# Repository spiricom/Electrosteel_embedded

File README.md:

# Electrosteel_embedded
repository for embedded firmware and EAGLE design files for the Electrosteel

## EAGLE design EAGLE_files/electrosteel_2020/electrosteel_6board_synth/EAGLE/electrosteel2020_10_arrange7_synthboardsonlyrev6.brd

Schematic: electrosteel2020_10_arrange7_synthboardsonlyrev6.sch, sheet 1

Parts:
C15, C30: .1uf; C0603K; PARTNO CC0603KRX7R8BB104
C16: 22uf; PANASONIC_D; PARTNO EEE-1CA220NP
C20: 22pf; C0603; PARTNO CC0603JRNPO9BN220
C21, C22, C23, C24, C25, C26, C27, C29, C31, C32: 10uf; C1206K; PARTNO TMK316F106ZL-T
J1: 4P-2.0; HW4-2.0; PARTNO 110990030
J2: 105162-0001; PARTNO 105162-0001
JP12: PINHD-1X2; 1X02; PARTNO *DNP
L1: 2.2uH; BOURNS_SRP2010; PARTNO SRP2010-2R2M
PS1: UWE1215S-3WR3; CONV_UWE1215S-3WR3; PARTNO UWE1215S-3WR3
R1, R2, R8, R13, R16, R19, R22: 10k; R0603; PARTNO ESR03EZPF1002
R3: 560R; R0603; PARTNO ESR03EZPF5600
R5, R93, R94, R95, R96, R97: 47k; R0603; PARTNO ESR03EZPJ473
R6, R7, R9, R12, R14, R15, R17, R18, R20, R21, R23, R56: 2M; R0603; PARTNO RMCF0603FT2M00
R24, R25: 2k; R0603; PARTNO ERJ-PA3F2001V
R27, R29, R30, R31, R32, R33, R34: 47R; R0603; PARTNO RC0603JR-0747RL
S1: 10-XX; B3F-10XX
U1: OPA1611AID; SOIC127P599X175-8N; PARTNO OPA1611AID
U2, U3, U4, U5, U6, U7, U8, U9, U10, U11: ES_DAISY_SEED_DOUBLE; PARTNO 4840-6004-CP
X1: 2516-; PAK100/2500-16; PARTNO SBH11-PBPC-D08-ST-BK

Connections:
+3V3: J2.4 (VDD), R24.1, R25.1, R93.2, R94.2, R95.2, R96.2, R97.2, U7.38 (+3V3_D), U7.B38 (+3V3_D)
+12V: C24.1, L1.P$1, U2.39 (V_IN), U2.B39 (V_IN), U3.39 (V_IN), U3.B39 (V_IN), U4.39 (V_IN), U4.B39 (V_IN), U5.39 (V_IN), U5.B39 (V_IN), U6.39 (V_IN), U6.B39 (V_IN), U7.39 (V_IN), U7.B39 (V_IN), U8.39 (V_IN), U8.B39 (V_IN), U9.39 (V_IN), U9.B39 (V_IN), U10.39 (V_IN), U10.B39 (V_IN), U11.39 (V_IN), U11.B39 (V_IN), X1.1, X1.3
+15V: C30.1, C32.1, PS1.6 (+VO), R6.2, R9.2, R14.2, R17.2, R20.2, R23.2, U1.7 (V+)
-15V: C15.2, C23.2, PS1.8 (-VO), R7.1, R12.1, R15.1, R18.1, R21.1, R56.1, U1.4 (V-)
CLK: J2.5 (CLK), R32.2
CMD: J2.3 (CMD), R31.2
DAT0: J2.7 (DAT0), R33.2
DAT1: J2.8 (DAT1), R34.2
DAT2: J2.1 (DAT2), R29.2
DAT3: J2.2 (CD/DAT3), R30.2
DGND4: C22.2, C24.2, J2.6 (VSS), J2.10 (GND_1), J2.11 (GND_2), J2.12 (GND_3), J2.13 (GND_4), PS1.1 (GND), S1.3, S1.4 (P1), U2.20 (AGND), U2.35 (GPIO28(ADC11)), U2.37 (GPIO30(USB_HS_D+)), U2.40 (GND), U2.B20 (AGND), U2.B35 (GPIO28(ADC11)), U2.B37 (GPIO30(USB_HS_D+)), U2.B40 (GND), U3.20 (AGND), U3.36 (GPIO29(USB_HS_D_-)), U3.37 (GPIO30(USB_HS_D+)), U3.40 (GND), U3.B20 (AGND), U3.B36 (GPIO29(USB_HS_D_-)), U3.B37 (GPIO30(USB_HS_D+)), U3.B40 (GND), U4.20 (AGND), U4.35 (GPIO28(ADC11)), U4.37 (GPIO30(USB_HS_D+)), U4.40 (GND), U4.B20 (AGND), U4.B35 (GPIO28(ADC11)), U4.B37 (GPIO30(USB_HS_D+)), U4.B40 (GND), U5.20 (AGND), U5.37 (GPIO30(USB_HS_D+)), U5.40 (GND), U5.B20 (AGND), U5.B37 (GPIO30(USB_HS_D+)), U5.B40 (GND), U6.20 (AGND), U6.35 (GPIO28(ADC11)), U6.36 (GPIO29(USB_HS_D_-)), U6.40 (GND), U6.B20 (AGND), U6.B35 (GPIO28(ADC11)), U6.B36 (GPIO29(USB_HS_D_-)), U6.B40 (GND), U7.20 (AGND), U7.35 (GPIO28(ADC11)), U7.36 (GPIO29(USB_HS_D_-)), U7.37 (GPIO30(USB_HS_D+)), U7.40 (GND), U7.B20 (AGND), U7.B35 (GPIO28(ADC11)), U7.B36 (GPIO29(USB_HS_D_-)), U7.B37 (GPIO30(USB_HS_D+)), U7.B40 (GND), U8.20 (AGND), U8.36 (GPIO29(USB_HS_D_-)), U8.40 (GND), U8.B20 (AGND), U8.B36 (GPIO29(USB_HS_D_-)), U8.B40 (GND), U9.20 (AGND), U9.37 (GPIO30(USB_HS_D+)), U9.40 (GND), U9.B20 (AGND), U9.B37 (GPIO30(USB_HS_D+)), U9.B40 (GND), U10.20 (AGND), U10.35 (GPIO28(ADC11)), U10.36 (GPIO29(USB_HS_D_-)), U10.40 (GND), U10.B20 (AGND), U10.B35 (GPIO28(ADC11)), U10.B36 (GPIO29(USB_HS_D_-)), U10.B40 (GND), U11.20 (AGND), U11.36 (GPIO29(USB_HS_D_-)), U11.40 (GND), U11.B20 (AGND), U11.B36 (GPIO29(USB_HS_D_-)), U11.B40 (GND), X1.2, X1.4
GNDINT: C15.1, C23.1, C30.2, C32.2, J1.3, J1.4, JP12.2, PS1.7 (0V), R5.1, U1.3 (+IN)
I2C_SCL: R24.2, U2.12 (GPIO11(I2C1_SCL)), U2.B12 (GPIO11(I2C1_SCL)), U3.12 (GPIO11(I2C1_SCL)), U3.B12 (GPIO11(I2C1_SCL)), U4.12 (GPIO11(I2C1_SCL)), U4.B12 (GPIO11(I2C1_SCL)), U5.12 (GPIO11(I2C1_SCL)), U5.B12 (GPIO11(I2C1_SCL)), U6.12 (GPIO11(I2C1_SCL)), U6.B12 (GPIO11(I2C1_SCL)), U7.12 (GPIO11(I2C1_SCL)), U7.B12 (GPIO11(I2C1_SCL)), U8.12 (GPIO11(I2C1_SCL)), U8.B12 (GPIO11(I2C1_SCL)), U9.12 (GPIO11(I2C1_SCL)), U9.B12 (GPIO11(I2C1_SCL)), U10.12 (GPIO11(I2C1_SCL)), U10.B12 (GPIO11(I2C1_SCL)), U11.12 (GPIO11(I2C1_SCL)), U11.B12 (GPIO11(I2C1_SCL))
I2C_SDA: R25.2, U2.13 (GPIO12(I2C1_SDA)), U2.B13 (GPIO12(I2C1_SDA)), U3.13 (GPIO12(I2C1_SDA)), U3.B13 (GPIO12(I2C1_SDA)), U4.13 (GPIO12(I2C1_SDA)), U4.B13 (GPIO12(I2C1_SDA)), U5.13 (GPIO12(I2C1_SDA)), U5.B13 (GPIO12(I2C1_SDA)), U6.13 (GPIO12(I2C1_SDA)), U6.B13 (GPIO12(I2C1_SDA)), U7.13 (GPIO12(I2C1_SDA)), U7.B13 (GPIO12(I2C1_SDA)), U8.13 (GPIO12(I2C1_SDA)), U8.B13 (GPIO12(I2C1_SDA)), U9.13 (GPIO12(I2C1_SDA)), U9.B13 (GPIO12(I2C1_SDA)), U10.13 (GPIO12(I2C1_SDA)), U10.B13 (GPIO12(I2C1_SDA)), U11.13 (GPIO12(I2C1_SDA)), U11.B13 (GPIO12(I2C1_SDA))
MASTER_SIGNAL: U2.1 (GPIO0(USB_HS_ID)), U2.B1 (GPIO0(USB_HS_ID)), U3.1 (GPIO0(USB_HS_ID)), U3.B1 (GPIO0(USB_HS_ID)), U4.1 (GPIO0(USB_HS_ID)), U4.B1 (GPIO0(USB_HS_ID)), U5.1 (GPIO0(USB_HS_ID)), U5.B1 (GPIO0(USB_HS_ID)), U6.1 (GPIO0(USB_HS_ID)), U6.B1 (GPIO0(USB_HS_ID)), U7.1 (GPIO0(USB_HS_ID)), U7.B1 (GPIO0(USB_HS_ID)), U8.1 (GPIO0(USB_HS_ID)), U8.B1 (GPIO0(USB_HS_ID)), U9.1 (GPIO0(USB_HS_ID)), U9.B1 (GPIO0(USB_HS_ID)), U10.1 (GPIO0(USB_HS_ID)), U10.B1 (GPIO0(USB_HS_ID)), U11.1 (GPIO0(USB_HS_ID)), U11.B1 (GPIO0(USB_HS_ID))
MISO_2: R27.1, U7.10 (GPIO9(SPI1_MISO)), U7.B10 (GPIO9(SPI1_MISO))
MISO_2_P1: U3.10 (GPIO9(SPI1_MISO)), U3.B10 (GPIO9(SPI1_MISO))
MISO_2_P2: U4.10 (GPIO9(SPI1_MISO)), U4.B10 (GPIO9(SPI1_MISO))
MISO_2_P3: U5.10 (GPIO9(SPI1_MISO)), U5.B10 (GPIO9(SPI1_MISO))
MISO_2_P4: U6.10 (GPIO9(SPI1_MISO)), U6.B10 (GPIO9(SPI1_MISO))
MISO_2_P5: U8.10 (GPIO9(SPI1_MISO)), U8.B10 (GPIO9(SPI1_MISO))
MISO_2_P6: U2.10 (GPIO9(SPI1_MISO)), U2.B10 (GPIO9(SPI1_MISO))
MISO_2_P7: U9.10 (GPIO9(SPI1_MISO)), U9.B10 (GPIO9(SPI1_MISO))
MISO_2_P8: U10.10 (GPIO9(SPI1_MISO)), U10.B10 (GPIO9(SPI1_MISO))
MISO_2_P9: U11.10 (GPIO9(SPI1_MISO)), U11.B10 (GPIO9(SPI1_MISO))
MONO_OUTPUT: C16.+, C20.2, R2.2, U1.6 (OUT)
MOSI_2: U2.11 (GPIO10(SPI1_MOSI)), U2.B11 (GPIO10(SPI1_MOSI)), U3.11 (GPIO10(SPI1_MOSI)), U3.B11 (GPIO10(SPI1_MOSI)), U4.11 (GPIO10(SPI1_MOSI)), U4.B11 (GPIO10(SPI1_MOSI)), U5.11 (GPIO10(SPI1_MOSI)), U5.B11 (GPIO10(SPI1_MOSI)), U6.11 (GPIO10(SPI1_MOSI)), U6.B11 (GPIO10(SPI1_MOSI)), U7.11 (GPIO10(SPI1_MOSI)), U7.B11 (GPIO10(SPI1_MOSI)), U8.11 (GPIO10(SPI1_MOSI)), U8.B11 (GPIO10(SPI1_MOSI)), U9.11 (GPIO10(SPI1_MOSI)), U9.B11 (GPIO10(SPI1_MOSI)), U10.11 (GPIO10(SPI1_MOSI)), U10.B11 (GPIO10(SPI1_MOSI)), U11.11 (GPIO10(SPI1_MOSI)), U11.B11 (GPIO10(SPI1_MOSI)), X1.12
unnamed: U5.31 (GPIO24(ADC9)), U5.B31 (GPIO24(ADC9))
unnamed: C21.2, R6.1, R7.2, R8.1
unnamed: U6.31 (GPIO24(ADC9)), U6.B31 (GPIO24(ADC9))
unnamed: C20.1, R1.2, R2.1, R8.2, R13.2, R16.2, R19.2, R22.2, U1.2 (-IN)
unnamed: C16.-, R3.1
unnamed: J1.1, J1.2, JP12.1, R3.2, R5.2
unnamed: C25.2, R1.1, R23.1, R56.2
unnamed: C26.2, R9.1, R12.2, R13.1
unnamed: C27.2, R14.1, R15.2, R16.1
unnamed: C29.2, R17.1, R18.2, R19.1
unnamed: C31.2, R20.1, R21.2, R22.1
unnamed: U7.19 (AUDIO_OUT_R), U7.B19 (AUDIO_OUT_R)
unnamed: U7.17 (AUDIO_IN_R), U7.B17 (AUDIO_IN_R)
unnamed: U7.16 (AUDIO_IN_L), U7.B16 (AUDIO_IN_L)
unnamed: U7.15 (GPIO14(USART1_RX)), U7.B15 (GPIO14(USART1_RX))
unnamed: U2.21 (+3V3_A), U2.B21 (+3V3_A)
unnamed: U8.31 (GPIO24(ADC9)), U8.B31 (GPIO24(ADC9))
unnamed: U8.26 (GPIO19(ADC4)), U8.B26 (GPIO19(ADC4))
unnamed: U6.26 (GPIO19(ADC4)), U6.B26 (GPIO19(ADC4))
unnamed: U7.34 (GPIO27(SAI2_FS_B)), U7.B34 (GPIO27(SAI2_FS_B))
unnamed: U7.33 (GPIO26(SAI2_SD_A)), U7.B33 (GPIO26(SAI2_SD_A))
unnamed: U7.32 (GPIO25(ADC10)), U7.B32 (GPIO25(ADC10))
unnamed: U5.26 (GPIO19(ADC4)), U5.B26 (GPIO19(ADC4))
unnamed: R27.2, X1.11
unnamed: U7.28 (GPIO21(ADC6)), U7.B28 (GPIO21(ADC6))
unnamed: U7.27 (GPIO20(ADC5)), U7.B27 (GPIO20(ADC5))
unnamed: U4.26 (GPIO19(ADC4)), U4.B26 (GPIO19(ADC4))
unnamed: U3.26 (GPIO19(ADC4)), U3.B26 (GPIO19(ADC4))
unnamed: U3.21 (+3V3_A), U3.B21 (+3V3_A)
unnamed: U7.24 (GPIO17(ADC2)), U7.B24 (GPIO17(ADC2))
unnamed: U7.23 (GPIO16(ADC1)), U7.B23 (GPIO16(ADC1))
unnamed: U7.22 (GPIO15(ADC0)), U7.B22 (GPIO15(ADC0))
unnamed: U3.19 (AUDIO_OUT_R), U3.B19 (AUDIO_OUT_R)
unnamed: U3.17 (AUDIO_IN_R), U3.B17 (AUDIO_IN_R)
unnamed: U3.16 (AUDIO_IN_L), U3.B16 (AUDIO_IN_L)
unnamed: U3.15 (GPIO14(USART1_RX)), U3.B15 (GPIO14(USART1_RX))
unnamed: U3.14 (GPIO13(USART1_TX)), U3.B14 (GPIO13(USART1_TX))
unnamed: U7.26 (GPIO19(ADC4)), U7.B26 (GPIO19(ADC4))
unnamed: U3.35 (GPIO28(ADC11)), U3.38 (+3V3_D), U3.B35 (GPIO28(ADC11)), U3.B38 (+3V3_D)
unnamed: U3.34 (GPIO27(SAI2_FS_B)), U3.B34 (GPIO27(SAI2_FS_B))
unnamed: U3.33 (GPIO26(SAI2_SD_A)), U3.B33 (GPIO26(SAI2_SD_A))
unnamed: U3.32 (GPIO25(ADC10)), U3.B32 (GPIO25(ADC10))
unnamed: U3.28 (GPIO21(ADC6)), U3.B28 (GPIO21(ADC6))
unnamed: U3.27 (GPIO20(ADC5)), U3.B27 (GPIO20(ADC5))
unnamed: U7.21 (+3V3_A), U7.B21 (+3V3_A)
unnamed: U3.24 (GPIO17(ADC2)), U3.B24 (GPIO17(ADC2))
unnamed: U3.23 (GPIO16(ADC1)), U3.B23 (GPIO16(ADC1))
unnamed: U3.22 (GPIO15(ADC0)), U3.B22 (GPIO15(ADC0))
unnamed: U4.21 (+3V3_A), U4.B21 (+3V3_A)
unnamed: U4.19 (AUDIO_OUT_R), U4.B19 (AUDIO_OUT_R)
unnamed: U4.17 (AUDIO_IN_R), U4.B17 (AUDIO_IN_R)
unnamed: U4.16 (AUDIO_IN_L), U4.B16 (AUDIO_IN_L)
unnamed: U4.15 (GPIO14(USART1_RX)), U4.B15 (GPIO14(USART1_RX))
unnamed: U4.14 (GPIO13(USART1_TX)), U4.B14 (GPIO13(USART1_TX))
unnamed: S1.1 (S), S1.2 (S1), U7.14 (GPIO13(USART1_TX)), U7.B14 (GPIO13(USART1_TX))
unnamed: U3.2 (GPIO1(SDMMC1_D3)), U3.B2 (GPIO1(SDMMC1_D3))
unnamed: U4.34 (GPIO27(SAI2_FS_B)), U4.B34 (GPIO27(SAI2_FS_B))
unnamed: U4.33 (GPIO26(SAI2_SD_A)), U4.B33 (GPIO26(SAI2_SD_A))
unnamed: U4.32 (GPIO25(ADC10)), U4.B32 (GPIO25(ADC10))
unnamed: U4.28 (GPIO21(ADC6)), U4.B28 (GPIO21(ADC6))
unnamed: U4.27 (GPIO20(ADC5)), U4.B27 (GPIO20(ADC5))
unnamed: U4.24 (GPIO17(ADC2)), U4.B24 (GPIO17(ADC2))
unnamed: U4.23 (GPIO16(ADC1)), U4.B23 (GPIO16(ADC1))
unnamed: U4.22 (GPIO15(ADC0)), U4.B22 (GPIO15(ADC0))
unnamed: U5.21 (+3V3_A), U5.B21 (+3V3_A)
unnamed: U5.19 (AUDIO_OUT_R), U5.B19 (AUDIO_OUT_R)
unnamed: U5.17 (AUDIO_IN_R), U5.B17 (AUDIO_IN_R)
unnamed: U5.16 (AUDIO_IN_L), U5.B16 (AUDIO_IN_L)
unnamed: U5.15 (GPIO14(USART1_RX)), U5.B15 (GPIO14(USART1_RX))
unnamed: U5.14 (GPIO13(USART1_TX)), U5.B14 (GPIO13(USART1_TX))
unnamed: U3.3 (GPIO2(SDMMC1_D2)), U3.B3 (GPIO2(SDMMC1_D2))
unnamed: U3.4 (GPIO3(SDMMC1_D1)), U3.B4 (GPIO3(SDMMC1_D1))
unnamed: U5.34 (GPIO27(SAI2_FS_B)), U5.B34 (GPIO27(SAI2_FS_B))
unnamed: U5.33 (GPIO26(SAI2_SD_A)), U5.B33 (GPIO26(SAI2_SD_A))
unnamed: U5.32 (GPIO25(ADC10)), U5.B32 (GPIO25(ADC10))
unnamed: U5.28 (GPIO21(ADC6)), U5.B28 (GPIO21(ADC6))
unnamed: U5.27 (GPIO20(ADC5)), U5.B27 (GPIO20(ADC5))
unnamed: U5.24 (GPIO17(ADC2)), U5.B24 (GPIO17(ADC2))
unnamed: U5.23 (GPIO16(ADC1)), U5.B23 (GPIO16(ADC1))
unnamed: U5.22 (GPIO15(ADC0)), U5.B22 (GPIO15(ADC0))
unnamed: C22.1, L1.P$2, PS1.2 (VIN)
unnamed: U6.21 (+3V3_A), U6.B21 (+3V3_A)
unnamed: U6.19 (AUDIO_OUT_R), U6.B19 (AUDIO_OUT_R)
unnamed: U6.17 (AUDIO_IN_R), U6.B17 (AUDIO_IN_R)
unnamed: U6.16 (AUDIO_IN_L), U6.B16 (AUDIO_IN_L)
unnamed: U6.15 (GPIO14(USART1_RX)), U6.B15 (GPIO14(USART1_RX))
unnamed: U6.14 (GPIO13(USART1_TX)), U6.B14 (GPIO13(USART1_TX))
unnamed: U6.37 (GPIO30(USB_HS_D+)), U6.38 (+3V3_D), U6.B37 (GPIO30(USB_HS_D+)), U6.B38 (+3V3_D)
unnamed: U3.5 (GPIO4(SDMMC1_D0)), U3.B5 (GPIO4(SDMMC1_D0))
unnamed: U6.34 (GPIO27(SAI2_FS_B)), U6.B34 (GPIO27(SAI2_FS_B))
unnamed: U6.33 (GPIO26(SAI2_SD_A)), U6.B33 (GPIO26(SAI2_SD_A))
unnamed: U6.32 (GPIO25(ADC10)), U6.B32 (GPIO25(ADC10))
unnamed: U6.28 (GPIO21(ADC6)), U6.B28 (GPIO21(ADC6))
unnamed: U6.27 (GPIO20(ADC5)), U6.B27 (GPIO20(ADC5))
unnamed: U6.24 (GPIO17(ADC2)), U6.B24 (GPIO17(ADC2))
unnamed: U6.23 (GPIO16(ADC1)), U6.B23 (GPIO16(ADC1))
unnamed: U6.22 (GPIO15(ADC0)), U6.B22 (GPIO15(ADC0))
unnamed: U8.21 (+3V3_A), U8.B21 (+3V3_A)
unnamed: U8.19 (AUDIO_OUT_R), U8.B19 (AUDIO_OUT_R)
unnamed: U8.17 (AUDIO_IN_R), U8.B17 (AUDIO_IN_R)
unnamed: U8.16 (AUDIO_IN_L), U8.B16 (AUDIO_IN_L)
unnamed: U8.15 (GPIO14(USART1_RX)), U8.B15 (GPIO14(USART1_RX))
unnamed: U8.14 (GPIO13(USART1_TX)), U8.B14 (GPIO13(USART1_TX))
unnamed: U8.35 (GPIO28(ADC11)), U8.37 (GPIO30(USB_HS_D+)), U8.38 (+3V3_D), U8.B35 (GPIO28(ADC11)), U8.B37 (GPIO30(USB_HS_D+)), U8.B38 (+3V3_D)
unnamed: U3.6 (GPIO5(SDMMC1_CMD)), U3.B6 (GPIO5(SDMMC1_CMD))
unnamed: U3.7 (GPIO6(SDMMC1_CK)), U3.B7 (GPIO6(SDMMC1_CK))
unnamed: U2.19 (AUDIO_OUT_R), U2.B19 (AUDIO_OUT_R)
unnamed: U8.34 (GPIO27(SAI2_FS_B)), U8.B34 (GPIO27(SAI2_FS_B))
unnamed: U8.33 (GPIO26(SAI2_SD_A)), U8.B33 (GPIO26(SAI2_SD_A))
unnamed: U8.32 (GPIO25(ADC10)), U8.B32 (GPIO25(ADC10))
unnamed: U8.28 (GPIO21(ADC6)), U8.B28 (GPIO21(ADC6))
unnamed: U8.27 (GPIO20(ADC5)), U8.B27 (GPIO20(ADC5))
unnamed: U8.24 (GPIO17(ADC2)), U8.B24 (GPIO17(ADC2))
unnamed: U8.23 (GPIO16(ADC1)), U8.B23 (GPIO16(ADC1))
unnamed: U8.22 (GPIO15(ADC0)), U8.B22 (GPIO15(ADC0))
unnamed: U4.2 (GPIO1(SDMMC1_D3)), U4.B2 (GPIO1(SDMMC1_D3))
unnamed: U4.3 (GPIO2(SDMMC1_D2)), U4.B3 (GPIO2(SDMMC1_D2))
unnamed: U4.4 (GPIO3(SDMMC1_D1)), U4.B4 (GPIO3(SDMMC1_D1))
unnamed: U4.5 (GPIO4(SDMMC1_D0)), U4.B5 (GPIO4(SDMMC1_D0))
unnamed: U4.6 (GPIO5(SDMMC1_CMD)), U4.B6 (GPIO5(SDMMC1_CMD))
unnamed: U4.7 (GPIO6(SDMMC1_CK)), U4.B7 (GPIO6(SDMMC1_CK))
unnamed: U2.17 (AUDIO_IN_R), U2.B17 (AUDIO_IN_R)
unnamed: U5.2 (GPIO1(SDMMC1_D3)), U5.B2 (GPIO1(SDMMC1_D3))
unnamed: U5.3 (GPIO2(SDMMC1_D2)), U5.B3 (GPIO2(SDMMC1_D2))
unnamed: U5.4 (GPIO3(SDMMC1_D1)), U5.B4 (GPIO3(SDMMC1_D1))
unnamed: U5.5 (GPIO4(SDMMC1_D0)), U5.B5 (GPIO4(SDMMC1_D0))
unnamed: U5.6 (GPIO5(SDMMC1_CMD)), U5.B6 (GPIO5(SDMMC1_CMD))
unnamed: U5.7 (GPIO6(SDMMC1_CK)), U5.B7 (GPIO6(SDMMC1_CK))
unnamed: U2.16 (AUDIO_IN_L), U2.B16 (AUDIO_IN_L)
unnamed: U6.2 (GPIO1(SDMMC1_D3)), U6.B2 (GPIO1(SDMMC1_D3))
unnamed: U6.3 (GPIO2(SDMMC1_D2)), U6.B3 (GPIO2(SDMMC1_D2))
unnamed: U6.4 (GPIO3(SDMMC1_D1)), U6.B4 (GPIO3(SDMMC1_D1))
unnamed: U6.5 (GPIO4(SDMMC1_D0)), U6.B5 (GPIO4(SDMMC1_D0))
unnamed: U6.6 (GPIO5(SDMMC1_CMD)), U6.B6 (GPIO5(SDMMC1_CMD))
unnamed: U6.7 (GPIO6(SDMMC1_CK)), U6.B7 (GPIO6(SDMMC1_CK))
unnamed: U8.2 (GPIO1(SDMMC1_D3)), U8.B2 (GPIO1(SDMMC1_D3))
unnamed: U8.3 (GPIO2(SDMMC1_D2)), U8.B3 (GPIO2(SDMMC1_D2))
unnamed: U8.4 (GPIO3(SDMMC1_D1)), U8.B4 (GPIO3(SDMMC1_D1))
unnamed: U8.5 (GPIO4(SDMMC1_D0)), U8.B5 (GPIO4(SDMMC1_D0))
unnamed: U8.6 (GPIO5(SDMMC1_CMD)), U8.B6 (GPIO5(SDMMC1_CMD))
unnamed: U8.7 (GPIO6(SDMMC1_CK)), U8.B7 (GPIO6(SDMMC1_CK))
unnamed: U2.15 (GPIO14(USART1_RX)), U2.B15 (GPIO14(USART1_RX))
unnamed: U2.14 (GPIO13(USART1_TX)), U2.B14 (GPIO13(USART1_TX))
unnamed: U2.34 (GPIO27(SAI2_FS_B)), U2.B34 (GPIO27(SAI2_FS_B))
unnamed: U2.33 (GPIO26(SAI2_SD_A)), U2.B33 (GPIO26(SAI2_SD_A))
unnamed: U2.32 (GPIO25(ADC10)), U2.B32 (GPIO25(ADC10))
unnamed: U2.28 (GPIO21(ADC6)), U2.B28 (GPIO21(ADC6))
unnamed: U2.27 (GPIO20(ADC5)), U2.B27 (GPIO20(ADC5))
unnamed: U2.24 (GPIO17(ADC2)), U2.B24 (GPIO17(ADC2))
unnamed: U2.23 (GPIO16(ADC1)), U2.B23 (GPIO16(ADC1))
unnamed: U2.22 (GPIO15(ADC0)), U2.B22 (GPIO15(ADC0))
unnamed: U9.21 (+3V3_A), U9.B21 (+3V3_A)
unnamed: U9.19 (AUDIO_OUT_R), U9.B19 (AUDIO_OUT_R)
unnamed: U9.17 (AUDIO_IN_R), U9.B17 (AUDIO_IN_R)
unnamed: U9.16 (AUDIO_IN_L), U9.B16 (AUDIO_IN_L)
unnamed: U9.15 (GPIO14(USART1_RX)), U9.B15 (GPIO14(USART1_RX))
unnamed: U9.14 (GPIO13(USART1_TX)), U9.B14 (GPIO13(USART1_TX))
unnamed: U9.34 (GPIO27(SAI2_FS_B)), U9.B34 (GPIO27(SAI2_FS_B))
unnamed: U9.33 (GPIO26(SAI2_SD_A)), U9.B33 (GPIO26(SAI2_SD_A))
unnamed: U9.32 (GPIO25(ADC10)), U9.B32 (GPIO25(ADC10))
unnamed: U9.28 (GPIO21(ADC6)), U9.B28 (GPIO21(ADC6))
unnamed: U9.27 (GPIO20(ADC5)), U9.B27 (GPIO20(ADC5))
unnamed: U9.24 (GPIO17(ADC2)), U9.B24 (GPIO17(ADC2))
unnamed: U9.23 (GPIO16(ADC1)), U9.B23 (GPIO16(ADC1))
unnamed: U9.22 (GPIO15(ADC0)), U9.B22 (GPIO15(ADC0))
unnamed: U10.21 (+3V3_A), U10.B21 (+3V3_A)
unnamed: U10.19 (AUDIO_OUT_R), U10.B19 (AUDIO_OUT_R)
unnamed: U10.17 (AUDIO_IN_R), U10.B17 (AUDIO_IN_R)
unnamed: U10.16 (AUDIO_IN_L), U10.B16 (AUDIO_IN_L)
unnamed: U10.15 (GPIO14(USART1_RX)), U10.B15 (GPIO14(USART1_RX))
unnamed: U10.14 (GPIO13(USART1_TX)), U10.B14 (GPIO13(USART1_TX))
unnamed: U10.37 (GPIO30(USB_HS_D+)), U10.38 (+3V3_D), U10.B37 (GPIO30(USB_HS_D+)), U10.B38 (+3V3_D)
unnamed: U10.34 (GPIO27(SAI2_FS_B)), U10.B34 (GPIO27(SAI2_FS_B))
unnamed: U10.33 (GPIO26(SAI2_SD_A)), U10.B33 (GPIO26(SAI2_SD_A))
unnamed: U10.32 (GPIO25(ADC10)), U10.B32 (GPIO25(ADC10))
unnamed: U10.28 (GPIO21(ADC6)), U10.B28 (GPIO21(ADC6))
unnamed: U10.27 (GPIO20(ADC5)), U10.B27 (GPIO20(ADC5))
unnamed: U10.24 (GPIO17(ADC2)), U10.B24 (GPIO17(ADC2))
unnamed: U10.23 (GPIO16(ADC1)), U10.B23 (GPIO16(ADC1))
unnamed: U10.22 (GPIO15(ADC0)), U10.B22 (GPIO15(ADC0))
unnamed: U11.21 (+3V3_A), U11.B21 (+3V3_A)
unnamed: U11.19 (AUDIO_OUT_R), U11.B19 (AUDIO_OUT_R)
unnamed: U11.17 (AUDIO_IN_R), U11.B17 (AUDIO_IN_R)
unnamed: U11.16 (AUDIO_IN_L), U11.B16 (AUDIO_IN_L)
unnamed: U11.15 (GPIO14(USART1_RX)), U11.B15 (GPIO14(USART1_RX))
unnamed: U11.14 (GPIO13(USART1_TX)), U11.B14 (GPIO13(USART1_TX))
unnamed: U11.35 (GPIO28(ADC11)), U11.37 (GPIO30(USB_HS_D+)), U11.38 (+3V3_D), U11.B35 (GPIO28(ADC11)), U11.B37 (GPIO30(USB_HS_D+)), U11.B38 (+3V3_D)
unnamed: U11.34 (GPIO27(SAI2_FS_B)), U11.B34 (GPIO27(SAI2_FS_B))
unnamed: U11.33 (GPIO26(SAI2_SD_A)), U11.B33 (GPIO26(SAI2_SD_A))
unnamed: U11.32 (GPIO25(ADC10)), U11.B32 (GPIO25(ADC10))
unnamed: U11.28 (GPIO21(ADC6)), U11.B28 (GPIO21(ADC6))
unnamed: U11.27 (GPIO20(ADC5)), U11.B27 (GPIO20(ADC5))
unnamed: U11.24 (GPIO17(ADC2)), U11.B24 (GPIO17(ADC2))
unnamed: U11.23 (GPIO16(ADC1)), U11.B23 (GPIO16(ADC1))
unnamed: U11.22 (GPIO15(ADC0)), U11.B22 (GPIO15(ADC0))
unnamed: U9.31 (GPIO24(ADC9)), U9.B31 (GPIO24(ADC9))
unnamed: U10.31 (GPIO24(ADC9)), U10.B31 (GPIO24(ADC9))
unnamed: U11.31 (GPIO24(ADC9)), U11.B31 (GPIO24(ADC9))
unnamed: U11.26 (GPIO19(ADC4)), U11.B26 (GPIO19(ADC4))
unnamed: U10.26 (GPIO19(ADC4)), U10.B26 (GPIO19(ADC4))
unnamed: U9.26 (GPIO19(ADC4)), U9.B26 (GPIO19(ADC4))
unnamed: U2.26 (GPIO19(ADC4)), U2.B26 (GPIO19(ADC4))
unnamed: U2.2 (GPIO1(SDMMC1_D3)), U2.B2 (GPIO1(SDMMC1_D3))
unnamed: U2.3 (GPIO2(SDMMC1_D2)), U2.B3 (GPIO2(SDMMC1_D2))
unnamed: U2.4 (GPIO3(SDMMC1_D1)), U2.B4 (GPIO3(SDMMC1_D1))
unnamed: U2.5 (GPIO4(SDMMC1_D0)), U2.B5 (GPIO4(SDMMC1_D0))
unnamed: U2.6 (GPIO5(SDMMC1_CMD)), U2.B6 (GPIO5(SDMMC1_CMD))
unnamed: U2.7 (GPIO6(SDMMC1_CK)), U2.B7 (GPIO6(SDMMC1_CK))
unnamed: U9.2 (GPIO1(SDMMC1_D3)), U9.B2 (GPIO1(SDMMC1_D3))
unnamed: U9.3 (GPIO2(SDMMC1_D2)), U9.B3 (GPIO2(SDMMC1_D2))
unnamed: U9.4 (GPIO3(SDMMC1_D1)), U9.B4 (GPIO3(SDMMC1_D1))
unnamed: U9.5 (GPIO4(SDMMC1_D0)), U9.B5 (GPIO4(SDMMC1_D0))
unnamed: U9.6 (GPIO5(SDMMC1_CMD)), U9.B6 (GPIO5(SDMMC1_CMD))
unnamed: U9.7 (GPIO6(SDMMC1_CK)), U9.B7 (GPIO6(SDMMC1_CK))
unnamed: U10.2 (GPIO1(SDMMC1_D3)), U10.B2 (GPIO1(SDMMC1_D3))
unnamed: U10.3 (GPIO2(SDMMC1_D2)), U10.B3 (GPIO2(SDMMC1_D2))
unnamed: U10.4 (GPIO3(SDMMC1_D1)), U10.B4 (GPIO3(SDMMC1_D1))
unnamed: U10.5 (GPIO4(SDMMC1_D0)), U10.B5 (GPIO4(SDMMC1_D0))
unnamed: U10.6 (GPIO5(SDMMC1_CMD)), U10.B6 (GPIO5(SDMMC1_CMD))
unnamed: U10.7 (GPIO6(SDMMC1_CK)), U10.B7 (GPIO6(SDMMC1_CK))
unnamed: U11.2 (GPIO1(SDMMC1_D3)), U11.B2 (GPIO1(SDMMC1_D3))
unnamed: U11.3 (GPIO2(SDMMC1_D2)), U11.B3 (GPIO2(SDMMC1_D2))
unnamed: U11.4 (GPIO3(SDMMC1_D1)), U11.B4 (GPIO3(SDMMC1_D1))
unnamed: U11.5 (GPIO4(SDMMC1_D0)), U11.B5 (GPIO4(SDMMC1_D0))
unnamed: U11.6 (GPIO5(SDMMC1_CMD)), U11.B6 (GPIO5(SDMMC1_CMD))
unnamed: U11.7 (GPIO6(SDMMC1_CK)), U11.B7 (GPIO6(SDMMC1_CK))
OUT1: C25.1, U7.18 (AUDIO_OUT_L), U7.B18 (AUDIO_OUT_L)
OUT2: C21.1, U3.18 (AUDIO_OUT_L), U3.B18 (AUDIO_OUT_L)
OUT3: C26.1, U2.18 (AUDIO_OUT_L), U2.B18 (AUDIO_OUT_L), U4.18 (AUDIO_OUT_L), U4.B18 (AUDIO_OUT_L)
OUT4: C27.1, U5.18 (AUDIO_OUT_L), U5.B18 (AUDIO_OUT_L), U9.18 (AUDIO_OUT_L), U9.B18 (AUDIO_OUT_L)
OUT5: C29.1, U6.18 (AUDIO_OUT_L), U6.B18 (AUDIO_OUT_L), U10.18 (AUDIO_OUT_L), U10.B18 (AUDIO_OUT_L)
OUT6: C31.1, U8.18 (AUDIO_OUT_L), U8.B18 (AUDIO_OUT_L), U11.18 (AUDIO_OUT_L), U11.B18 (AUDIO_OUT_L)
PA1_SD_DETECT: J2.9 (DET), U3.31 (GPIO24(ADC9)), U3.B31 (GPIO24(ADC9)), U7.31 (GPIO24(ADC9)), U7.B31 (GPIO24(ADC9))
PA1_SD_DETECT1: U4.31 (GPIO24(ADC9)), U4.B31 (GPIO24(ADC9))
PA1_SD_DETECT2: U2.31 (GPIO24(ADC9)), U2.B31 (GPIO24(ADC9))
PULLUPED: U5.35 (GPIO28(ADC11)), U5.36 (GPIO29(USB_HS_D_-)), U5.38 (+3V3_D), U5.B35 (GPIO28(ADC11)), U5.B36 (GPIO29(USB_HS_D_-)), U5.B38 (+3V3_D), U9.35 (GPIO28(ADC11)), U9.36 (GPIO29(USB_HS_D_-)), U9.38 (+3V3_D), U9.B35 (GPIO28(ADC11)), U9.B36 (GPIO29(USB_HS_D_-)), U9.B38 (+3V3_D)
PULLUPED2: U2.36 (GPIO29(USB_HS_D_-)), U2.38 (+3V3_D), U2.B36 (GPIO29(USB_HS_D_-)), U2.B38 (+3V3_D), U4.36 (GPIO29(USB_HS_D_-)), U4.38 (+3V3_D), U4.B36 (GPIO29(USB_HS_D_-)), U4.B38 (+3V3_D)
SCLK_2: U2.9 (GPIO8(SPI1_SCK)), U2.B9 (GPIO8(SPI1_SCK)), U3.9 (GPIO8(SPI1_SCK)), U3.B9 (GPIO8(SPI1_SCK)), U4.9 (GPIO8(SPI1_SCK)), U4.B9 (GPIO8(SPI1_SCK)), U5.9 (GPIO8(SPI1_SCK)), U5.B9 (GPIO8(SPI1_SCK)), U6.9 (GPIO8(SPI1_SCK)), U6.B9 (GPIO8(SPI1_SCK)), U7.9 (GPIO8(SPI1_SCK)), U7.B9 (GPIO8(SPI1_SCK)), U8.9 (GPIO8(SPI1_SCK)), U8.B9 (GPIO8(SPI1_SCK)), U9.9 (GPIO8(SPI1_SCK)), U9.B9 (GPIO8(SPI1_SCK)), U10.9 (GPIO8(SPI1_SCK)), U10.B9 (GPIO8(SPI1_SCK)), U11.9 (GPIO8(SPI1_SCK)), U11.B9 (GPIO8(SPI1_SCK)), X1.10
SD_CLK: R32.1, U7.7 (GPIO6(SDMMC1_CK)), U7.B7 (GPIO6(SDMMC1_CK))
SD_CMD: R31.1, R95.1, U7.6 (GPIO5(SDMMC1_CMD)), U7.B6 (GPIO5(SDMMC1_CMD))
SD_DAT0: R33.1, R94.1, U7.5 (GPIO4(SDMMC1_D0)), U7.B5 (GPIO4(SDMMC1_D0))
SD_DAT1: R34.1, R93.1, U7.4 (GPIO3(SDMMC1_D1)), U7.B4 (GPIO3(SDMMC1_D1))
SD_DAT2: R29.1, R97.1, U7.3 (GPIO2(SDMMC1_D2)), U7.B3 (GPIO2(SDMMC1_D2))
SD_DAT3: R30.1, R96.1, U7.2 (GPIO1(SDMMC1_D3)), U7.B2 (GPIO1(SDMMC1_D3))
SPI6_CLK: U2.29 (GPIO22(ADC7/DAC2)), U2.B29 (GPIO22(ADC7/DAC2)), U3.29 (GPIO22(ADC7/DAC2)), U3.B29 (GPIO22(ADC7/DAC2)), U4.29 (GPIO22(ADC7/DAC2)), U4.B29 (GPIO22(ADC7/DAC2)), U5.29 (GPIO22(ADC7/DAC2)), U5.B29 (GPIO22(ADC7/DAC2)), U6.29 (GPIO22(ADC7/DAC2)), U6.B29 (GPIO22(ADC7/DAC2)), U7.29 (GPIO22(ADC7/DAC2)), U7.B29 (GPIO22(ADC7/DAC2)), U8.29 (GPIO22(ADC7/DAC2)), U8.B29 (GPIO22(ADC7/DAC2)), U9.29 (GPIO22(ADC7/DAC2)), U9.B29 (GPIO22(ADC7/DAC2)), U10.29 (GPIO22(ADC7/DAC2)), U10.B29 (GPIO22(ADC7/DAC2)), U11.29 (GPIO22(ADC7/DAC2)), U11.B29 (GPIO22(ADC7/DAC2)), X1.6
SPI6_MOSI: U2.25 (GPIO18(ADC3)), U2.B25 (GPIO18(ADC3)), U3.25 (GPIO18(ADC3)), U3.B25 (GPIO18(ADC3)), U4.25 (GPIO18(ADC3)), U4.B25 (GPIO18(ADC3)), U5.25 (GPIO18(ADC3)), U5.B25 (GPIO18(ADC3)), U6.25 (GPIO18(ADC3)), U6.B25 (GPIO18(ADC3)), U7.25 (GPIO18(ADC3)), U7.B25 (GPIO18(ADC3)), U8.25 (GPIO18(ADC3)), U8.B25 (GPIO18(ADC3)), U9.25 (GPIO18(ADC3)), U9.B25 (GPIO18(ADC3)), U10.25 (GPIO18(ADC3)), U10.B25 (GPIO18(ADC3)), U11.25 (GPIO18(ADC3)), U11.B25 (GPIO18(ADC3)), X1.8
SPI6_NSS: U2.30 (GPIO23(ADC8/DAC1)), U2.B30 (GPIO23(ADC8/DAC1)), U3.30 (GPIO23(ADC8/DAC1)), U3.B30 (GPIO23(ADC8/DAC1)), U4.30 (GPIO23(ADC8/DAC1)), U4.B30 (GPIO23(ADC8/DAC1)), U5.30 (GPIO23(ADC8/DAC1)), U5.B30 (GPIO23(ADC8/DAC1)), U6.30 (GPIO23(ADC8/DAC1)), U6.B30 (GPIO23(ADC8/DAC1)), U7.30 (GPIO23(ADC8/DAC1)), U7.B30 (GPIO23(ADC8/DAC1)), U8.30 (GPIO23(ADC8/DAC1)), U8.B30 (GPIO23(ADC8/DAC1)), U9.30 (GPIO23(ADC8/DAC1)), U9.B30 (GPIO23(ADC8/DAC1)), U10.30 (GPIO23(ADC8/DAC1)), U10.B30 (GPIO23(ADC8/DAC1)), U11.30 (GPIO23(ADC8/DAC1)), U11.B30 (GPIO23(ADC8/DAC1)), X1.5
SS_2: U2.8 (GPIO7(SPI1_NSS)), U2.B8 (GPIO7(SPI1_NSS)), U3.8 (GPIO7(SPI1_NSS)), U3.B8 (GPIO7(SPI1_NSS)), U4.8 (GPIO7(SPI1_NSS)), U4.B8 (GPIO7(SPI1_NSS)), U5.8 (GPIO7(SPI1_NSS)), U5.B8 (GPIO7(SPI1_NSS)), U6.8 (GPIO7(SPI1_NSS)), U6.B8 (GPIO7(SPI1_NSS)), U7.8 (GPIO7(SPI1_NSS)), U7.B8 (GPIO7(SPI1_NSS)), U8.8 (GPIO7(SPI1_NSS)), U8.B8 (GPIO7(SPI1_NSS)), U9.8 (GPIO7(SPI1_NSS)), U9.B8 (GPIO7(SPI1_NSS)), U10.8 (GPIO7(SPI1_NSS)), U10.B8 (GPIO7(SPI1_NSS)), U11.8 (GPIO7(SPI1_NSS)), U11.B8 (GPIO7(SPI1_NSS)), X1.9

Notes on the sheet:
Audio
000
001
010
011
100
101

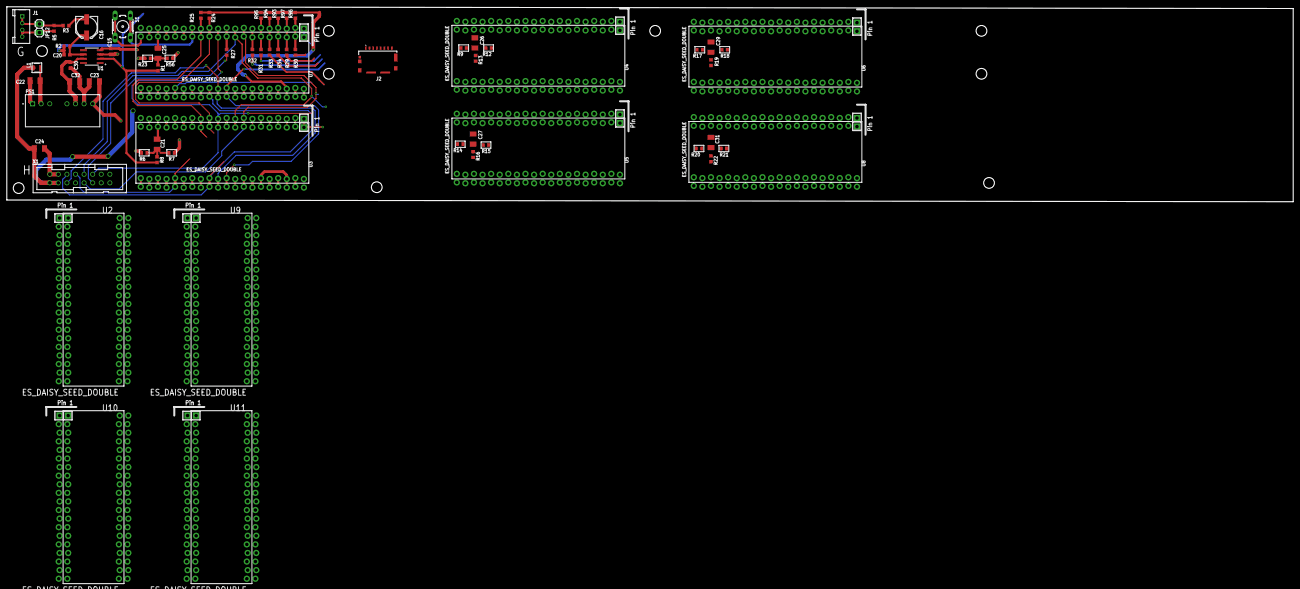
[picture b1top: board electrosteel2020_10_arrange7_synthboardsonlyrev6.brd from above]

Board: 4 copper layers, 380.5 x 57.7 mm, 67 parts (0 on the bottom side), 275 nets.

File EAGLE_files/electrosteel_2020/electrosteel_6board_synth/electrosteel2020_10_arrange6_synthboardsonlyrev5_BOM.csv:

Qty-1,Part References,Value,Package,Mfg Part Num,Mfg Name,VID,Vendor Part Num,Description,Pkg Code,XREF
1,"S1",,B3F-10XX,B3F-1000,Omron,DK,SW400-ND,SWITCH TACTILE SPST-NO 0.05A 24V,TH,REF13
2,"C15, C30",.1uf,C0603K,CC0603KRX7R8BB104,Yageo,DK,311-1341-1-ND,CAP CER 0.1UF 25V 10% X7R 0603,0603,REF14
1,"L1",2.2uH,BOURNS_SRP2010,SRP2010-2R2M,Bourns,DK,SRP2010-2R2MTR-ND,FIXED IND 2.2UH 1.7A 150MOHM SMD,0806,REF466
12,"R6, R7, R9, R12, R14, R15, R17, R18, R20, R21, R23, R56",2M,R0603,RMCF0603FT2M00,Stackpole,DK,RMCF0603FT2M00TR-ND,RES 2M OHM 1% 1/10W 0603,0603,REF468
2,"R24, R25",2k,R0603,ERJ-PA3F2001V,Panasonic,DK,P2.00KBYCT-ND,RES SMD 2K OHM 1% 1/4W 0603,0603,REF247
1,"J1",4P-2.0,HW4-2.0,110990030,Seeed,MO,713-110990030,Seeed Studio Accessories Grove - Universal 4 pin connector,TH,REF471
7,"R1, R2, R8, R13, R16, R19, R22",10k,R0603,ESR03EZPF1002,Rohm,DK,RHM10KADCT-ND,RES 10K OHM 1/4W 1% 0603 SMD,0603,REF106
10,"C21, C22, C23, C24, C25, C26, C27, C29, C31, C32",10uf,C1206K,TMK316F106ZL-T,Taiyo,DK,587-1353-1-ND,CAP CER 10UF 25V Y5V 1206,1206,REF180
1,"C20",22pf,C0603,CC0603JRNPO9BN220,Yageo,DK,311-1062-1-ND,CAP CER 22PF 50V 5% NPO 0603,0603,REF21
1,"C16",22uf,PANASONIC_D,EEE-1CA220NP,Panasonic,DK,PCE4306CT-ND,CAP ALUM 22UF 20% 16V SMD Bipolar,PANASONIC_C,REF387
7,"R27, R29, R30, R31, R32, R33, R34",47R,R0603,RC0603JR-0747RL,Yageo,DK,311-47GRCT-ND,RES SMD 47 OHM 5% 1/10W 0603,0603,REF314
6,"R5, R93, R94, R95, R96, R97",47k,R0603,ESR03EZPJ473,Rohm,DK,RHM47KDCT-ND,RES 47K OHM 1/4W 5% 0603 SMD,0603,REF117
1,"R3",560R,R0603,ESR03EZPF5600,Rohm,DK,RHM560ADCT-ND,RES 560 OHM 1/4W 1% 0603 SMD,0603,REF128
1,"X1",2516-,PAK100/2500-16,SBH11-PBPC-D08-ST-BK,Sullins,DK,S9171-ND,16 Positions Shrouded Header .100" Dual,TH,REF246
1,"J2",105162-0001,105162-0001,105162-0001,Molex,MO,538-105162-0001,Memory Card Connectors 1.45H MICRO SD HEADER WITH D/C PIN,SMD,REF465
6,"U3, U4, U5, U6, U7, U8",ES_DAISY_SEED_DOUBLE,ES_DAISY_SEED_DOUBLE,4840-6004-CP,3M,DK,3M5483-ND,40 (2 x 20) Pos DIP, 0.6" (15.24mm) Row Spacing Socket Tin Through Hole,TH,REF470
1,"U1",OPA1611AID,SOIC127P599X175-8N,OPA1611AID,TI,DK,296-24958-5-ND,Audio Amplifier 1 Circuit 8-SOIC,8-SOIC,REF469
1,"JP12",PINHD-1X2,1X02,*DNP,DO NOT PLACE,(N/A),DO NOT PLACE,DO NOT PLACE,*,REF2
1,"PS1",UWE1215S-3WR3,CONV_UWE1215S-3WR3,UWE1215S-3WR3,Mornsun,DK,2725-UWE1215S-3WR3-ND,Isolated Module DC DC Converter 2 Output 15V -15V 100mA, 100mA 4.5V - 36V Input,TH,REF467

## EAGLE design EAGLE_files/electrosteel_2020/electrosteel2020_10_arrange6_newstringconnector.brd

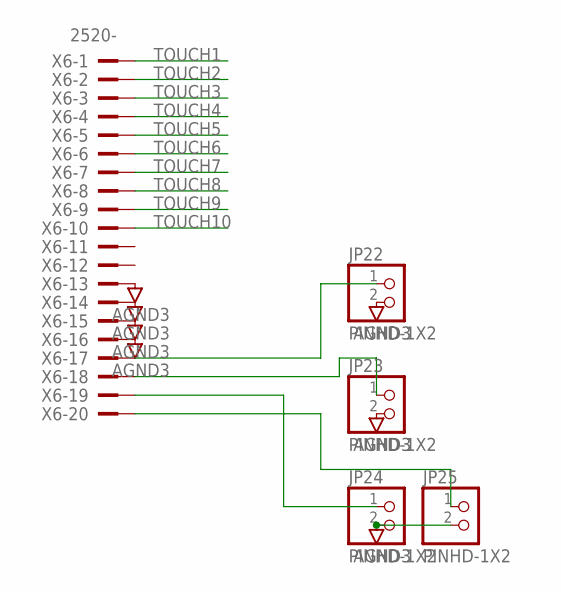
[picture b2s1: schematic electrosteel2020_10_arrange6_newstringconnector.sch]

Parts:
JP22, JP23, JP24, JP25: PINHD-1X2; 1X02; PARTNO *DNP
X6: 2520-; PAK100/2500-20; PARTNO N2520-6003-UG

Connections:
AGND3: JP22.2, JP23.2, JP24.2, JP25.2, X6.13, X6.14, X6.15, X6.16
unnamed: JP24.1, X6.19
unnamed: JP25.1, X6.20
unnamed: JP23.1, X6.18
unnamed: JP22.1, X6.17
TOUCH1: X6.1
TOUCH2: X6.2
TOUCH3: X6.3
TOUCH4: X6.4
TOUCH5: X6.5
TOUCH6: X6.6
TOUCH7: X6.7
TOUCH8: X6.8
TOUCH9: X6.9
TOUCH10: X6.10

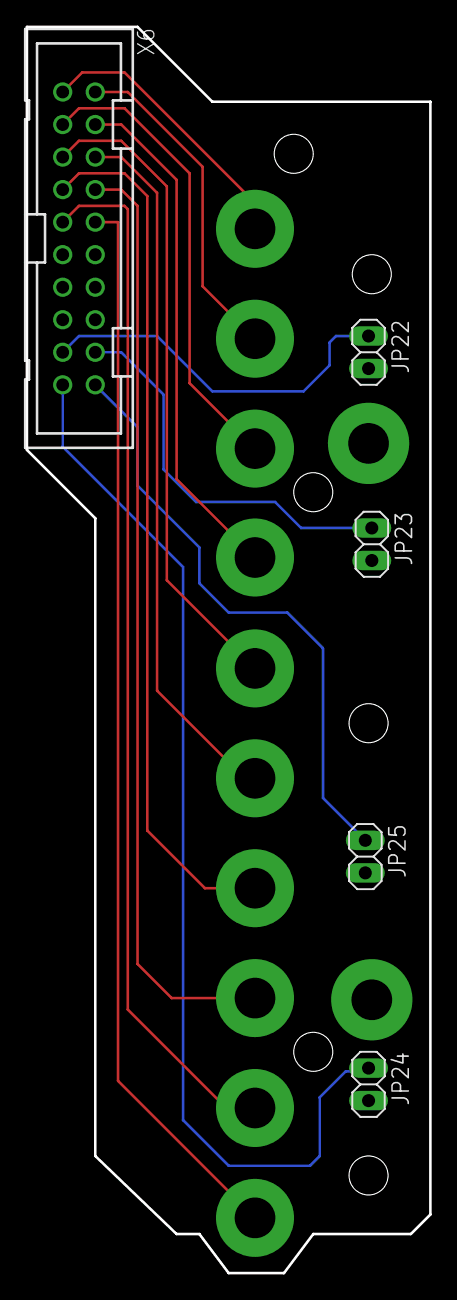
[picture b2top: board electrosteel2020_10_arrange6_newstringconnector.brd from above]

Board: 4 copper layers, 31.5 x 97.3 mm, 5 parts (0 on the bottom side), 5 nets.

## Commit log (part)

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2022-12-08 adding psoc code
2022-12-08 added string pluck sensor code
2022-12-08 added EAGLE files
2022-12-08 added electrosteel audio code
2022-12-08 added new fretboard to psoc code'
2022-12-14 new string touch sensor pcb code
2022-12-30 stupid
2022-12-31 improved bar timing and testing sine wave synthesis
2022-12-31 new version of psoc code that uses current dac and lower res slider
2022-12-31 copied in electrobass synthesis, still mono though
2023-01-03 working electrosteel, doesnt take in new patches but reads electrobass patches off sdcard
2023-01-05 optimized, and now expecting new data format from brain
2023-01-05 new brain sending format, brain now takes copedents from plugin and stores them in one of 7 slots on the brain
2023-01-06 current code loads presets
2023-01-08 working electrosteel psoc code. added code to skip unconnected pedals and lever in the i2c communication. also added calibration mode to set the min and max of the levers
2023-01-08 fixed storage of copedents and calibration data so that it doesn't overlap
2023-01-09 macro knobs sensing correctly, and sped things up by commenting out midi computation of pitch bend for computer communication. Will need to put that back in once the plugin can handle it
2023-01-09 knob displays working
2023-01-09 improved the bar sensing psoc code by increasing the range of the adc, decreasing the resolution of the adc for speed reasons, and boosting the idac current slightly to fill the increased range
2023-01-17 eagle files for rev5 synthboard finished
2023-03-24 push before working
2023-04-26 started daisy version of audio boards for electrosteel
2023-04-29 got one new synthboard working, doesnt yet send firmware over i2c to other boards
2023-05-07 working on daisy port. one board works but subsequent voices still dont always wake up at startup
2023-05-11 trying daisy pc
2023-05-11 trying daisy mac
2023-05-15 working for plork session
2023-05-21 working code for electrosteel using daisy. problem was mpu settings and not waiting for qspi init before writing firmware update
2023-05-22 working daisy electrosteel, tested with all 6 boards at once. works smoothly on many presets but fails on some presets that genera version could handle. need to explore why
2023-05-22 cache invalidate seems to solve issues
2023-05-22 working very well, now need to see if SDRAM memory can run faster
2023-05-23 sdram working ok. added back additive model and got string models to both use sram instead of sdram (freeing and initing as needed).
2023-05-25 changed pluck detection stm32 to be more sensitive for electromagnetic pickup. works great!;
2023-05-28 pedal mappings working in synth presets, and fixed a pluck scaling issue
2023-07-19 added capability to stream data from computer for realtime parameter changes
2023-07-19 added gitignore
2023-07-19 added psoc version of streaming capability
2023-07-20 working on getting mapping streaming functional, its close
2023-07-20 psoc side of mapping stream sending
2023-08-04 includes bootloader
2023-08-05 changed font, added name size limits, fixed macro knob midi sending
2023-08-07 many changes with close to a working menu system, and changes to slider resolution of the bar
2023-08-08 added working transpose feature, although it doesnt yet send to the synthesis
2023-08-09 fixed volume bug on every other string, and did some cleanup;
2023-08-12 added knob freezing (untested) and corrected harmonic number calculation in stm32 code
2023-08-12 fixed octave midi send bug, and other things
2023-08-21 updating
2023-09-04 new version
2023-09-09 restructed pluck to put memory in DTCMRAM and removed last two strings to leave it at 10 strings
2023-09-10 testing with int type changes to uint_fast8_t etc. breaks things, may have to do with MPU settings and things now going over alignment breaks.
2023-09-16 changed pluck communication to 32 bytes to align to cache size and avoid alignment errors. Finished writing code to allow pluck firmware update from synth board, but then realized that the pluck IC c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
2023-09-20 little details
2023-10-17 changed priorities of spi and adc dma controllers in pluck mcu
2023-12-01 version after london
2023-12-28 added genera version for testing, and refactored files into multiple c and h, and added tTstring
2024-01-03 added string model with dispersion, tension, phantom harmonics, and rudimentary bar slide noise
2024-01-08 good working version on custom chip with new tTString ;
2024-01-10 good version of tTString and ready to test moving it to the Daisy board
2024-01-10 just changed CMSIS DSP library in daisy board
2024-01-14 vocal improved, string good
2024-01-15 working ability to store versions of nonsynth models
2024-01-15 added Cypress brain sending local preset storage data
2024-01-16 fixed ability to store locally normal synth presets
2024-01-18 preset storage stuff
2024-01-22 many small fixes and replaced CMSIS DSP oversampling with my custom one because it was messing up he gain
2024-02-05 changed volume pedal curve, fixed vocal nan, and in the middle of transferring to bootloader version
2024-02-06 shipped version 1, added internal naming of presets in sd card write, transferred to daisy board
2024-02-12 many small fixes including storing preset bug and frozen knob bug
2024-02-12 fixed many small bugs including knobFrozen bug and initialization knob settings bug
2024-02-19 improved filters, and made hardware and software more similar, added transpose ability
2024-04-15 big changes
2024-04-15 fixed copedent receive bug and added firmware version reporting
2025-04-24 current state
2025-12-27 new version, preparing for new pcb spin for 2025
2025-12-29 kicad file updated with 10 synth boards[
2026-01-04 working on sensor circuit
2026-01-04 good single channel of fretboard rev
2026-01-04 version with three coil circuits, some errors
2026-01-04 got 6 of em
2026-01-04 all circuit traces
2026-01-04 all circuit traces, fixed circuit 2
2026-01-04 all circuit traces,in position
2026-01-06 stm32 micro added
2026-01-06 mcu configured, still needs power connections and spi i2c connections
2026-01-08 finished routing - adding silkscreen
2026-01-08 silkscreen finished
2026-01-08 mostly done, adjusting silkscreen labels
2026-01-09 exported gerbers of lefthand
2026-01-10 almost done with circuits, changing sd card reader
2026-01-10 finished bom and centroid
2026-03-06 got new left hand sensor working with SENT receive on stm32 chip. still requires very wide bar and doesnt yet send to the brain microcontroller or do interpolation
2026-03-08 all 9 sensors for new left hand are working and reporting properly via SENT, working on getting transmission to other boards
2026-03-08 some kicad edits
2026-03-12 testing on genera brain for synth of pattistring
2026-03-13 worked on tPattistring implementation
2026-03-21 new test circuits for bar sensor
2026-04-08 'update'
2026-04-08 added bend range settings
2026-04-12 rhino files
2026-04-15 kicad stuff
2026-04-20 testing 96k
2026-04-22 96k version working, but physical models broken, and currently doesnt have smooth way to change samplerate with 96kdefine
2026-04-22 got 96k working
2026-04-26 in the middle of changing it
2026-04-27 changed knobs back to tExpSmooth due to too heavy a load from tDynamicSmoother
2026-05-23 updated to have 24/48 bend range, but broke note ons
2026-05-30 new brain board firmware now stores fret calibration properly but doesnt yet read it properly

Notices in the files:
parts and their libraries:
SparkFun-IC-Microcontroller: Licensing: Creative Commons ShareAlike 4.0 International - https://creativecommons.org/licenses/by-sa/4.0
con-headers-jp: Copyright (C) 2008, Bob Starr
PatternAgents-Beautify: License : http://creativecommons.org/licenses/by-sa/3.0
(Creative Commons 3.0)
